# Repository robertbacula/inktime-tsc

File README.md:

# InkTime v6 - Smartwatch Open Hardware cu E-Paper

InkTime v6 este un proiect hardware open-source de smartwatch bazat pe nRF52840, optimizat pentru consum redus, autonomie mare si integrare mecanica compacta. Documentatia de mai jos este structurata pentru review tehnic si include arhitectura sistemului, BOM, maparea pinilor, analiza de consum si observatii de design.

## Cuprins

- [Diagrama bloc](#diagrama-bloc)
- [Bill of Materials (BOM)](#bill-of-materials-bom)
- [Functionalitate hardware detaliata](#functionalitate-hardware-detaliata)
- [Maparea pinilor nRF52840](#maparea-pinilor-nrf52840)
- [Analiza consumului de energie](#analiza-consumului-de-energie)
- [Design PCB si integrare mecanica](#design-pcb-si-integrare-mecanica)
- [Design log si observatii pentru review](#design-log-si-observatii-pentru-review)
- [Structura repository-ului](#structura-repository-ului)
- [Licenta](#licenta)

## Diagrama bloc

Diagrama bloc este prezentata ca imagine:

Flux de functionare:

1. USB-C alimenteaza incarcatorul BQ25180 si bateria LiPo.
2. Din baterie se genereaza rail-ul de 3.3V (RT6160A), comutat catre sarcina prin PMOS.
3. nRF52840 colecteaza date de la IMU/fuel gauge si controleaza display-ul prin SPI.
4. Pentru notificari locale, nRF52840 activeaza DRV2605 care comanda motorul haptic.
5. BLE asigura schimb de date si configurare cu telefonul.

## Bill of Materials (BOM)

Tabelul de mai jos acopera componentele principale. Pentru pasivele individuale, consultati schema si listele de asamblare exportate din CAD.

| #   | Ref  | Componenta              | Cod / Valoare     | JLC Parts                                                                                                 | Datasheet                                                                                                        |
| --- | ---- | ----------------------- | ----------------- | --------------------------------------------------------------------------------------------------------- | ---------------------------------------------------------------------------------------------------------------- |
| 1   | U1   | MCU BLE                 | nRF52840-QIAA     | [C190794](https://jlcpcb.com/parts/componentSearch?isSearch=true&searchTxt=nRF52840)                      | [nRF52840 PS](https://infocenter.nordicsemi.com/pdf/nRF52840_PS_v1.8.pdf)                                        |
| 2   | IC2  | Li-Ion Charger          | BQ25180YBGR       | [C2682092](https://jlcpcb.com/parts/componentSearch?isSearch=true&searchTxt=BQ25180)                      | [TI BQ25180](https://www.ti.com/lit/ds/symlink/bq25180.pdf)                                                      |
| 3   | IC9  | Buck DC/DC              | RT6160AWSC        | [C2828036](https://jlcpcb.com/parts/componentSearch?isSearch=true&searchTxt=RT6160A)                      | [Richtek RT6160A](https://www.richtek.com/assets/product_file/RT6160A/DS6160A-05.pdf)                            |
| 4   | U3   | Fuel Gauge              | MAX17048G+T10     | [C2682766](https://jlcpcb.com/parts/componentSearch?isSearch=true&searchTxt=MAX17048)                     | [MAX17048/49](https://datasheets.maximintegrated.com/en/ds/MAX17048-MAX17049.pdf)                                |
| 5   | IC3  | IMU                     | BMA423            | [C2831316](https://jlcpcb.com/parts/componentSearch?isSearch=true&searchTxt=BMA423)                       | [Bosch BMA423](https://www.bosch-sensortec.com/products/motion-sensors/accelerometers/bma423/)                   |
| 6   | IC1  | Driver haptic           | DRV2605YZFR       | [C527680](https://jlcpcb.com/parts/componentSearch?isSearch=true&searchTxt=DRV2605)                       | [TI DRV2605](https://www.ti.com/lit/ds/symlink/drv2605.pdf)                                                      |
| 7   | D1   | Protectie ESD USB       | USBLC6-2SC6Y      | [C7519](https://jlcpcb.com/parts/componentSearch?isSearch=true&searchTxt=USBLC6-2SC6Y)                    | [ST USBLC6-2](https://www.st.com/resource/en/datasheet/usblc6-2.pdf)                                             |
| 8   | Q1   | PMOS load switch        | DMG2305UX-7       | [C150812](https://jlcpcb.com/parts/componentSearch?isSearch=true&searchTxt=DMG2305UX)                     | [DMG2305UX](https://www.diodes.com/assets/Datasheets/DMG2305UX.pdf)                                              |
| 9   | Q3   | N-MOS (motor/periferic) | SI1308EDL-T1-GE3  | [C515086](https://jlcpcb.com/parts/componentSearch?isSearch=true&searchTxt=SI1308EDL)                     | [SI1308EDL](https://www.vishay.com/docs/68743/si1308edl.pdf)                                                     |
| 10  | J1   | FPC conector EPD        | 503480-2400 (24p) | [C585393](https://jlcpcb.com/parts/componentSearch?isSearch=true&searchTxt=503480-2400)                   | [Molex 503480](https://www.molex.com/pdm_docs/sd/5034802400_sd.pdf)                                              |
| 11  | J4   | USB-C conector          | KH-TYPE-C-16P     | [C2765186](https://jlcpcb.com/parts/componentSearch?isSearch=true&searchTxt=KH-TYPE-C-16P)                | [USB Type-C Spec](https://www.usb.org/document-library/usb-type-cr-cable-and-connector-specification-release-22) |
| 12  | ANT1 | Antena chip 2.4GHz      | 2450AT18B100E     | [Search JLC](https://jlcpcb.com/parts/componentSearch?isSearch=true&searchTxt=2450AT18B100E)              | [Johanson 2450AT18B100E](https://www.johansontechnology.com/datasheets/2450AT18B100E.pdf)                        |
| 13  | J2   | Header debug            | TC2030-IDC        | [Search JLC](https://jlcpcb.com/parts/componentSearch?isSearch=true&searchTxt=TC2030)                     | [Tag-Connect TC2030](https://www.tag-connect.com/wp-content/uploads/bsk-pdf-manager/TC2030-IDC-NL-10_NL_1.pdf)   |
| 14  | X1   | Cristal HF              | 32MHz             | [Search JLC](https://jlcpcb.com/parts/componentSearch?isSearch=true&searchTxt=32MHz%20crystal%202016)     | [Exemplu 32MHz](https://www.ecsxtal.com/store/pdf/ECS-160-12-33Q.pdf)                                            |
| 15  | X2   | Cristal LF              | 32.768kHz         | [Search JLC](https://jlcpcb.com/parts/componentSearch?isSearch=true&searchTxt=32.768kHz%20crystal%203215) | [Exemplu 32.768kHz](https://www.abracon.com/Resonators/ABS07.pdf)                                                |

## Functionalitate hardware detaliata

### 1) Procesare si conectivitate - nRF52840

- CPU: ARM Cortex-M4F @ 64MHz
- Memorie: 1MB Flash, 256KB RAM
- Radio: BLE 5.x la 2.4GHz
- Interfete folosite in proiect: SPI, I2C, GPIO, USB FS, SWD

Rol functional:

- ruleaza logica aplicatiei si machine-state-ul ceasului
- centralizeaza datele de la senzori
- controleaza secventa de refresh pentru e-paper
- gestioneaza notificari BLE si feedback haptic

### 2) Display e-paper (1.54") + etaj driver

Display-ul e-paper este comandat pe SPI, cu semnale separate de control (`DC`, `RST`, `BUSY`, `CS`). Avantajul major este consumul aproape zero in stare statica; energia se consuma aproape exclusiv la refresh.

Interfata:

- SPI pentru payload grafic
- GPIO pentru sincronizare/stare (`BUSY`) si comenzi

### 3) IMU BMA423

IMU-ul este conectat pe I2C si utilizat pentru:

- step counting
- wake-on-motion / wrist raise
- detectie evenimente contextuale

Poate genera intreruperi catre MCU pentru reducerea polling-ului si optimizare de consum.

### 4) Management baterie - BQ25180 + MAX17048 + RT6160A

- BQ25180: incarcare LiPo din VBUS (USB-C)
- MAX17048: monitorizare starea bateriei (SOC, tensiune)
- RT6160A: conversie stabila catre 3.3V pentru sistem

Acest lant permite operare corecta atat pe USB, cat si pe baterie, cu telemetrie energetica pentru estimarea autonomiei.

### 5) Haptic - DRV2605 + motor

DRV2605 genereaza profile haptice controlate de MCU (I2C + trigger), iar etajul de putere comuta motorul pentru feedback la notificari, alarme si interactiuni UI.

### 6) USB-C, protectie ESD si debug

- USB-C ofera VBUS pentru incarcare si (optional) date USB FS.
- USBLC6-2 reduce riscul de defect la descarcari electrostatice pe D+/D-.
- Header-ul TC2030 expune SWD pentru flash/debug si test de productie.

## Maparea pinilor nRF52840

Maparea de mai jos este cea utilizata in schema proiectului pentru functiile principale.

| Pin nRF52840  | Semnal / Componenta | Interfata | Directie | Motiv alegere                          |
| ------------- | ------------------- | --------- | -------- | -------------------------------------- |
| P0.02         | EPD_SCK             | SPI       | Out      | Clock stabil pentru transfer display   |
| P0.03         | EPD_MOSI            | SPI       | Out      | Date catre e-paper                     |
| P0.28         | EPD_MISO            | SPI       | In       | Citire status/date display             |
| P0.29         | EPD_CS              | GPIO/SPI  | Out      | Selectie dispozitiv e-paper            |
| P0.04         | EPD_DC              | GPIO      | Out      | Selectie data/comanda                  |
| P0.05         | EPD_RST             | GPIO      | Out      | Reset hardware display                 |
| P0.06         | EPD_BUSY            | GPIO      | In       | Sincronizare pe stare busy             |
| P0.26         | I2C_SDA             | I2C       | I/O      | Magistrala comuna senzori/power        |
| P0.27         | I2C_SCL             | I2C       | Out      | Clock I2C comun                        |
| P0.13         | SW_UP               | GPIO IRQ  | In       | Buton up, interrupt la apasare         |
| P0.14         | SW_ENT              | GPIO IRQ  | In       | Buton enter, UI action                 |
| P0.15         | SW_DN               | GPIO IRQ  | In       | Buton down, navigare                   |
| P0.18         | USB_D-              | USB FS    | I/O      | Linie USB dedicata (minus)             |
| P0.20         | USB_D+              | USB FS    | I/O      | Linie USB dedicata (plus)              |
| P0.00 / P0.01 | XL1 / XL2           | LFCLK     | I/O      | Cristal 32.768kHz pentru RTC low-power |
| XC1 / XC2     | X1 32MHz            | HFCLK     | I/O      | Ceas principal CPU/RF                  |
| SWDIO         | SWD_DATA            | SWD       | I/O      | Programare si debugging                |
| SWDCLK        | SWD_CLK             | SWD       | In       | Ceas SWD                               |
| SWO           | SWO_TRACE           | SWD       | Out      | Trace/telemetrie debug                 |
| ANT           | Antena BLE          | RF        | Out      | Iesire RF catre retea de matching      |

Rationale general pentru mapare:

1. SPI-ul display-ului este grupat compact pentru rutare scurta si integritate buna a semnalelor.
2. Toate perifericele lente (IMU, fuel gauge, haptic) sunt pe I2C comun pentru economie de pini.
3. Butoanele sunt pe GPIO-uri configurabile cu intreruperi, pentru wake-up din low power.
4. USB foloseste pinii dedicati ai MCU pentru compatibilitate fizica si software.

## Analiza consumului de energie

Estimare orientativa pe scenariu "smartwatch normal" (ecran actualizat periodic, BLE advertising, wake pe evenimente):

| Bloc                 | Curent activ | Curent sleep/idle | Duty cycle estimat | Curent mediu |
| -------------------- | -----------: | ----------------: | -----------------: | -----------: |
| nRF52840 (CPU + BLE) |  3.2mA-4.8mA |             1.5uA |               5-6% |       ~210uA |
| E-Paper (refresh)    |        ~15mA |       ~0uA static |               0.5% |        ~75uA |
| BMA423               |       ~150uA |             ~14uA |          10% activ |        ~28uA |
| MAX17048             |         23uA |              23uA |               100% |         23uA |
| DRV2605 + motor      |   ~50mA varf |           ~0.25uA |               0.1% |        ~50uA |
| RT6160A quiescent    |            - |             ~25uA |               100% |         25uA |
| **Total estimat**    |            - |                 - |                  - |   **~410uA** |

Pentru baterie de 250mAh:

- autonomie teoretica: `250mAh / 0.41mA = ~609h` (~25 zile)
- cu profil agresiv de sleep si refresh rar: 30-40+ zile (in functie de firmware si trafic BLE)

## Design PCB si integrare mecanica

### PCB

- layout realizat in fisierele `Hardware/project-tsc.sch` si `Hardware/project-tsc-2d-pcb.brd`
- topologia include zona RF dedicata, sectiune alimentare separata si trasee de semnal scurte catre conectorul EPD
- protectie ESD pe USB si puncte de test pentru bring-up

### Integrare mecanica

- modele 3D disponibile in `Mechanical/InkTime3D.f3z` si `Mechanical/InkTime3D.step`
- verificari importante: inaltime baterie, spatiu FPC display, pozitie butoane laterale, clearance pentru motorul haptic

## Design log si observatii pentru review

Design log (sintetic):

1. Definire arhitectura (MCU, putere, senzori, afisaj)
2. Captura schema si validare ERC
3. Placement cu prioritizare RF/power/display
4. Routing + optimizari DRC/ground return
5. Export productie si validare mecanica 3D

Observatii utile pentru review:

- verificati zona antenei: keepout de cupru sub antenna + matching network conform recomandari vendor
- confirmati polaritatea pentru bateria LiPo si sensul diodei Schottky
- verificati secventa de power-up EPD in firmware, pentru a evita refresh instabil
- recomandat test incremental: power rail -> SWD -> I2C -> EPD -> BLE

## Structura repository-ului

```text
inktime-tsc/
|- Hardware/
|  |- project-tsc.sch
|  |- project-tsc-2d-pcb.brd
|- Images/
|  |- 3dpcb.jpg
|  |- inktime-full-watch.jpg
|  |- inktime-3d-expanded-view.jpg
|  |- inktime-watch-no-screen.jpg
|- Manufacturing/
|  |- inktime_gerber.zip
|- Mechanical/
|  |- InkTime3D.f3z
|  |- InkTime3D.step
|- LICENSE
|- README.md
```

## Licenta

Proiectul este distribuit conform fisierului `LICENSE` din acest repository.

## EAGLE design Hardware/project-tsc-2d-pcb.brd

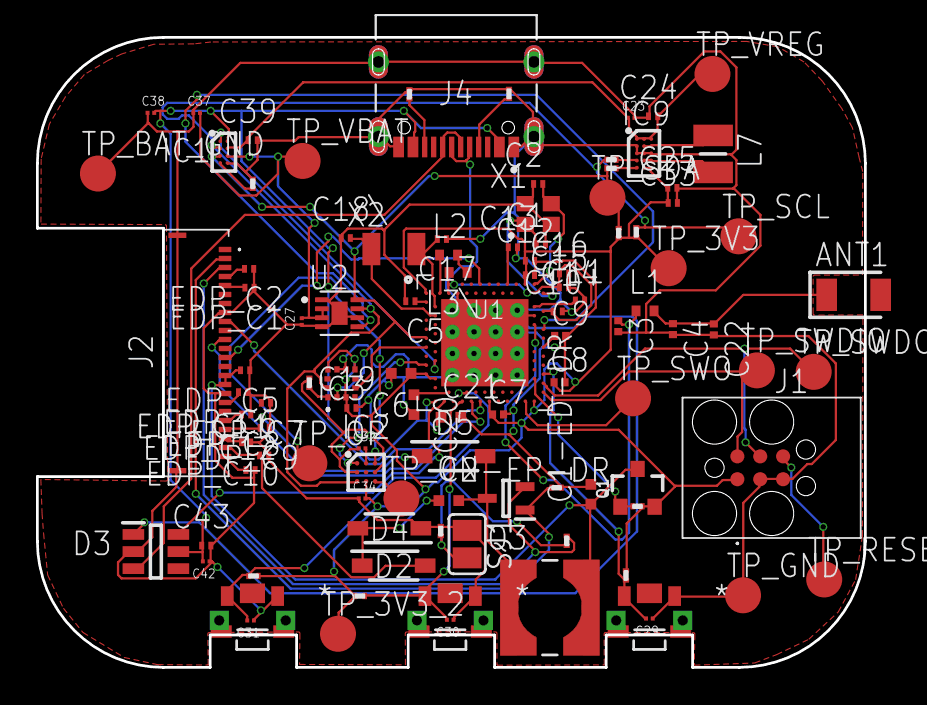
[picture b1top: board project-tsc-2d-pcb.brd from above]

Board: 2 copper layers, 46.0 x 35.0 mm, 105 parts (0 on the bottom side), 70 nets.

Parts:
ANT1: 2450AT18B100E; 2450AT18B100E_ANTC3216X140N
C1, C2, C17, C18\: 12pF; NORDIC_NRF_3_RESC0201_L
C1-ED-DR: 10uF; NORDIC_NRF_3_RESC0402_N
C2-EP-DR, C6, C20, C21: 4.7uF; NORDIC_NRF_3_RESC0402_N
C3, C4: 1pF; NORDIC_NRF_3_RESC0201_N
C5, C12, C19: 100nF; NORDIC_NRF_3_RESC0201_L
C7, C8: 100nF; NORDIC_NRF_3_RESC0201_N
C9: 820pF; NORDIC_NRF_3_RESC0201_N
C10, C13: N.C.; NORDIC_NRF_3_RESC0201_L
C11: 100pF; NORDIC_NRF_3_RESC0201_L
C14, C43: 4.7uF; NORDIC_NRF_3_RESC0201_L
C15: 1.0uF; NORDIC_NRF_3_RESC0201_L
C16: 47nF; NORDIC_NRF_3_RESC0201_L
C22: N.C.; NORDIC_NRF_3_RESC0201_N
C23, C27, C34, C42: 0.1uF; GRM011R60J152KE01L_2_CAPC0201X13N
C24, C39: 10uF; NORDIC_NRF_3_RESC0201_L
C25, C33: 22uF; NORDIC_NRF_3_RESC0201_L
C29, C30, C31, C32, C37, C38: 1uF; GRM011R60J152KE01L_2_CAPC0201X13N
D2, D4, D5: MBR0530; ESP32_C6_LIBRARY_5_SOD3716X135N
D3: USBLC6-2SC6Y; ESP32_C6_LIBRARY_3_SOT95P280X145-6N
EDP_C1, EDP_C2: 10uF; NORDIC_NRF_3_RESC0201_L
EDP_C5: 0.1uF/50V; NORDIC_NRF_3_RESC0201_L
EDP_C6, EDP_C7, EDP_C8, EDP_C9, EDP_C10, EDP_C11, EDP_C12: 1uF/50V; NORDIC_NRF_3_RESC0201_L
IC1: BQ25180YBGR; BQ25180YBGR_BGA8C40P2X4_100X155X50
IC2: DRV2605YZFR; DRV2605YZFR_BGA9C50P3X3_144X144X62
IC3: BMA421; BMA423_BMA423
IC9: RT6160AWSC; RT6160AWSC_BGA15C40P3X5_140X230X60
J1: TC2030-IDC_TC2030-IDC; TC2030-IDC_TC2030IDC
J2: 503480-2400_503480-2400; 503480-2400_5034802400
J4: KH-TYPE-C-16P; KH-TYPE-C-16P_KINGHELM_KH-TYPE-C-16P
L1: 3.9nH; NORDIC_NRF_2_RESC0402_L
L2: 10uH; NORDIC_NRF_2_RESC0402_L
L3\: 15nH; NORDIC_NRF_2_RESC0402_L
L5: 68uH; ESP32_C6_LIBRARY_2_IND_4828-WE-TPC_WRE
L7: FTC252012SR47MBCA; MLP2016SR47MT0S1_INDC2016X100N
Q1: 20V/4.2A/52mΩ/1.4W; ESP32_C6_LIBRARY_4_ESP32_C6_LIBRARY_4_ESP32_C6_LIBRARY_4_ES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
Q3: SI1308EDL-T1-GE3; ESP32_C6_LIBRARY_6_SOT65P210X110-3N
R1, R2, R2_EP_DR, R5, R7, R8, R9: 10K; CPF0201D7K68C1_0201
R1_EP_DR1: 0.47; CPF0201D7K68C1_0201
R1_USB, R2_USB: 5K1; CPF0201D7K68C1_0201
R3: 0; CPF0201D7K68C1_0201
R17, R18: 3K3; CPF0201D7K68C1_0201
R_PWR_EPD: 10K; CPF0201D7K68C1_0201
R_TYPE_SEL: 2.2; CPF0201D7K68C1_0201
SJ1: ESP32_C6_LIBRARY_7_JUMPER_SJ
SW_DN: 2025-10-22_07-23-44_LIBRARY_EVP-AKE31ASW_EVP-AKE3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; 2025-10-22_07-23-44_LIBRARY_SW_EVP-AKE31A_PAN
SW_ENT: 2025-10-22_07-23-44_LIBRARY_EVP-AKE31ASW_EVP-AKE3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; 2025-10-22_07-23-44_LIBRARY_SW_EVP-AKE31A_PAN
SW_UP: 2025-10-22_07-23-44_LIBRARY_EVP-AKE31ASW_EVP-AKE3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; 2025-10-22_07-23-44_LIBRARY_SW_EVP-AKE31A_PAN
TP_3V3, TP_3V3_2: HECTOR_WATCH_1_TPTP20R; HECTOR_WATCH_1_TP20R
TP_BAT_GND: HECTOR_WATCH_1_TPTP20R; HECTOR_WATCH_1_TP20R
TP_GND: HECTOR_WATCH_1_TPTP20R; HECTOR_WATCH_1_TP20R
TP_ON: HECTOR_WATCH_1_TPTP20R; HECTOR_WATCH_1_TP20R
TP_OP: HECTOR_WATCH_1_TPTP20R; HECTOR_WATCH_1_TP20R
TP_RESET: HECTOR_WATCH_1_TPTP20R; HECTOR_WATCH_1_TP20R
TP_SCL: HECTOR_WATCH_1_TPTP20R; HECTOR_WATCH_1_TP20R
TP_SDA: HECTOR_WATCH_1_TPTP20R; HECTOR_WATCH_1_TP20R
TP_SWDCLK: HECTOR_WATCH_1_TPTP20R; HECTOR_WATCH_1_TP20R
TP_SWDIO: HECTOR_WATCH_1_TPTP20R; HECTOR_WATCH_1_TP20R
TP_SWO: HECTOR_WATCH_1_TPTP20R; HECTOR_WATCH_1_TP20R
TP_VBAT: HECTOR_WATCH_1_TPTP20R; HECTOR_WATCH_1_TP20R
TP_VREG: HECTOR_WATCH_1_TPTP20R; HECTOR_WATCH_1_TP20R
U1: NRF52840_QF; NORDIC_NRF_4_AQFN50P700X700X85_HS-74N
U2: ESP32_C6_LIBRARY_MAX17048G+T10; ESP32_C6_LIBRARY_SON50P200X200X80-9N
X1: 32MHz; NORDIC_NRF_BT-XTAL_2016_N
X2: 32.726kHz; NORDIC_NRF_1_XTAL_3215_N

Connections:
3V1: C5.1, U1.P$C1
3V3: C6.1, C7.1, C8.1, C12.1, C14.1, C19.1, C25.1, C33.1, C34.2, IC2.C2, IC3.3, IC3.7, IC3.10, IC9.E2, IC9.E3, J1.1, Q1.2, R5.1, R7.1, R8.1, R17.2, R18.2, R_PWR_EPD.1, TP_3V3.TP, TP_3V3_2.TP, U1.P$A22, U1.P$AD14, U1.P$AD23, U1.P$B1, U1.P$W1, U1.P$Y2
ALERT: U1.P$J24, U2.5
D+: D3.4, U1.P$AD6
D-: D3.6, U1.P$AD4
DN: D3.1, J4.A7, J4.B7
DP: D3.3, J4.A6, J4.B6
EPD_3V3: C1-ED-DR.1, EDP_C5.2, J2.15, J2.16, L5.2, Q1.3
EPD_BUSY: J2.9, U1.P$AD12
EPD_CS: J2.12, U1.P$K2
EPD_DC: J2.11, U1.P$AD10
EPD_RST: J2.10, U1.P$AC11
ESP_3V1: EDP_C6.2, J2.18
ESP_3V2: EDP_C7.2, J2.19
ESP_3V4: EDP_C8.2, J2.20
ESP_3V6: EDP_C10.2, J2.22
GDR: J2.2, Q3.1, R2_EP_DR.1
GND: C1.2, C1-ED-DR.2, C2.1, C3.2, C4.2, C5.2, C6.2, C7.2, C8.2, C9.2, C10.2, C11.2, C12.2, C13.2, C14.2, C15.2, C16.2, C17.1, C18\.1, C19.2, C20.2, C21.2, C22.2, C23.2, C24.1, C25.2, C27.1, C29.1, C30.1, C31.1, C32.1, C33.2, C34.1, C37.1, C38.1, C39.2, C42.1, C43.2, D3.2, D4.1, EDP_C1.1, EDP_C2.1, EDP_C5.1, EDP_C6.1, EDP_C7.1, EDP_C8.1, EDP_C9.1, EDP_C10.1, EDP_C11.2, EDP_C12.2, IC1.D2, IC2.B1, IC2.B3, IC3.8, IC3.9, IC9.B1, IC9.C1, IC9.C2, IC9.C3, J1.3, J1.5, J2.8, J2.17, J2.MP1, J2.MP2, J4.A1_B12, J4.A12_B1, J4.SH1, J4.SH2, J4.SH3, J4.SH4, R1_USB.1, R2_EP_DR.2, R2_USB.2, R3.1, R9.1, R_TYPE_SEL.2, SJ1.1, SW_DN.1, SW_ENT.1, SW_UP.1, TP_BAT_GND.TP, TP_GND.TP, U1.P$74, U1.P$75, U1.P$76, U1.P$77, U1.P$78, U1.P$79, U1.P$80, U1.P$81, U1.P$82, U1.P$83, U1.P$84, U1.P$85, U1.P$86, U1.P$87, U1.P$88, U1.P$89, U1.P$90, U1.P$B7, U1.P$F23, U2.1, U2.4, U2.6, U2.9, X1.2, X1.4
GND1: C17.2, U1.P$D2, X2.2
GND2: C18\.2, U1.P$F2, X2.1
GND3: C2.2, U1.P$A23, X1.3
HAPTIC_EN: IC2.A1, U1.P$U1
IMU_INT1: IC3.5, U1.P$N1
IMU_INT2: IC3.6, U1.P$P2
LX1: IC9.B2, IC9.B3, L7.1
LX2: IC9.D2, IC9.D3, L7.2
MOSI: J2.14, U1.P$B13
unnamed: L2.1, U1.P$B3
unnamed: L2.2, L3\.1
unnamed: C10.1, C15.1, C16.1, L3\.2, U1.P$B5, U1.P$E24
unnamed: R1_EP_DR1.2, R_TYPE_SEL.1, SJ1.2
unnamed: IC1.D1, R9.2
unnamed: C2-EP-DR.2, D5.2, L5.1, Q3.3
unnamed: C2-EP-DR.1, D2.1, D4.2
unnamed: J4.A5, R1_USB.2
unnamed: J4.B5, R2_USB.1
unnamed: EDP_C2.2, J2.4
unnamed: EDP_C1.2, J2.5
unnamed: C32.2, IC2.A2
unnamed: C13.1, U1.P$A18
unnamed: C11.1, U1.P$D23
unnamed: C1.1, U1.P$B24, X1.1
unnamed: IC9.D1, R1.2
unnamed: IC9.E1, R2.2
unnamed: EDP_C12.1, J2.24
unnamed: IC3.1, R3.2
unnamed: C20.1, U1.P$AC5
unnamed: C9.1, U1.P$N24
unnamed: ANT1.1, C4.1, C22.1, L1.2
unnamed: C3.1, L1.1, U1.P$H23
OUT+: IC2.A3, TP_OP.TP
OUT-: IC2.C3, TP_ON.TP
P0.13: C30.2, R5.2, SW_UP.2, U1.P$AD8
P0.14: C31.2, R8.2, SW_ENT.2, U1.P$AC9
P1.01: Q1.1, R_PWR_EPD.2, U1.P$Y23
P1.02: C29.2, R7.2, SW_DN.2, U1.P$W24
PMIC_INT: IC1.A1, U1.P$T2
PREVGH: D5.1, EDP_C9.2, J2.21
PREVGL: D2.2, EDP_C11.1, J2.23
RESE: J2.3, Q3.2, R1_EP_DR1.1
RESET: J1.6, TP_RESET.TP, U1.P$AC13
SCK: J2.13, U1.P$A12
SCL: IC1.B1, IC2.C1, IC3.12, R1.1, R17.1, TP_SCL.TP, U1.P$M2, U2.7
SDA: IC1.C1, IC2.B2, IC3.2, R2.1, R18.1, TP_SDA.TP, U1.P$L1, U2.8
SWDCLK: J1.4, TP_SWDCLK.TP, U1.P$AA24
SWDIO: J1.2, TP_SWDIO.TP, U1.P$AC24
SWO: TP_SWO.TP, U1.P$AD22
VBAT: C27.2, C37.2, IC1.C2, TP_VBAT.TP, U2.2, U2.3
VBUS: C21.1, C38.2, C42.2, C43.1, D3.5, IC1.A2, J4.A4_B9, J4.A9_B4, U1.P$AD2
VREG: C23.1, C24.2, C39.1, IC1.B2, IC9.A1, IC9.A2, IC9.A3, TP_VREG.TP

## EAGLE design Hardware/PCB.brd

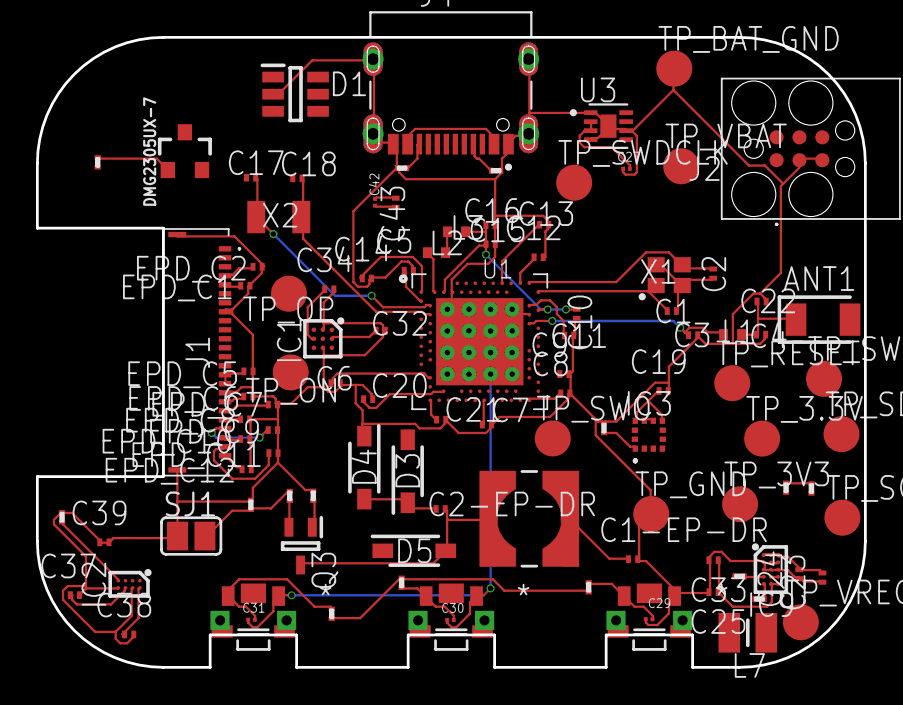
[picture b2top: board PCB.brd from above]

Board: 2 copper layers, 46.0 x 35.0 mm, 105 parts (0 on the bottom side), 63 nets.

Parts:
ANT1: 2450AT18B100E_2450AT18B100E; 2450AT18B100E_ANTC3216X140N
C1, C2, C17, C18: 12pF; NORDIC_NRF_3_RESC0201_L
C1-EP-DR: 10µF; NORDIC_NRF_3_RESC0201_L
C2-EP-DR: 4.7µF/25V; NORDIC_NRF_3_RESC0201_L
C3, C4: 1pF; NORDIC_NRF_3_RESC0201_L
C5, C7, C8, C12, C19: 100nF; NORDIC_NRF_3_RESC0201_L
C6, C14, C20, C21: 4.7µF; NORDIC_NRF_3_RESC0201_L
C9: 820pF; NORDIC_NRF_3_RESC0201_L
C10, C13, C15, C22: N.C.; NORDIC_NRF_3_RESC0201_L
C11: 100pF; NORDIC_NRF_3_RESC0201_L
C16: 27nF; NORDIC_NRF_3_RESC0201_L
C23: 0.1uF; NORDIC_NRF_3_RESC0201_L
C24: 10uF; NORDIC_NRF_3_RESC0201_L
C25, C33: 22uF; NORDIC_NRF_3_RESC0201_L
C27, C29, C30, C31, C42: GRM011R60J152KE01L_2_GRM011R60J152KE01L; GRM011R60J152KE01L_2_CAPC0201X13N
C32: 1µF; NORDIC_NRF_3_RESC0201_L
C34: 0.1µF; NORDIC_NRF_3_RESC0201_L
C37, C38, C39: NORDIC_NRF_3_RESC0201_L
C43: 4.7uF; NORDIC_NRF_3_RESC0201_L
D1: ESP32_C6_LIBRARY_3_USBLC6-2SC6Y; ESP32_C6_LIBRARY_3_SOT95P280X145-6N
D3, D4, D5: ESP32_C6_LIBRARY_5_MBR0530; ESP32_C6_LIBRARY_5_SOD3716X135N
DMG2305UX-7: 20V/4.2A/52mΩ/1.4W; ESP32_C6_LIBRARY_4_ESP32_C6_LIBRARY_4_ESP32_C6_LIBRARY_4_ES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
EPD_C1, EPD_C2: 1uF/50V; NORDIC_NRF_3_RESC0201_L
EPD_C5, EPD_C6, EPD_C7, EPD_C8, EPD_C9, EPD_C10, EPD_C11, EPD_C12: 0.1uF/50V; NORDIC_NRF_3_RESC0201_L
IC1: DRV2605YZFR_DRV2605YZFR; DRV2605YZFR_BGA9C50P3X3_144X144X62
IC2: BQ25180YBGR_BQ25180YBGR; BQ25180YBGR_BGA8C40P2X4_100X155X50
IC3: BMA423_BMA423
IC9: RT6160AWSC_RT6160AWSC; RT6160AWSC_BGA15C40P3X5_140X230X60
J1: 503480-2400_503480-2400; 503480-2400_5034802400
J2: TC2030-IDC_TC2030-IDC; TC2030-IDC_TC2030IDC
J4: KH-TYPE-C-16P_KH-TYPE-C-16P; KH-TYPE-C-16P_KINGHELM_KH-TYPE-C-16P
L1: 3.9nH; NORDIC_NRF_2_RESC0402_L
L2: 10µH; NORDIC_NRF_2_RESC0402_L
L3: 15nH; NORDIC_NRF_2_RESC0402_L
L5: 68uH; ESP32_C6_LIBRARY_2_IND_4828-WE-TPC_WRE
L7: MLP2016SR47MT0S1_FTC252012SR47MBCA; MLP2016SR47MT0S1_INDC2016X100N
Q3: ESP32_C6_LIBRARY_6_SI1308EDL-T1-GE3; ESP32_C6_LIBRARY_6_SOT65P210X110-3N
R1_EP_DR, R1_USB, R2, R2_EP_DR, R2_USB, R3, R4, R5, R7, R8, R9, R17, R18: ERA-1AEB3401C_CPF0201D7K68C1; ERA-1AEB3401C_0201
R_PWR_EPD: ERA-1AEB3401C_CPF0201D7K68C1; ERA-1AEB3401C_0201
R_TYPE_SEL: ERA-1AEB3401C_CPF0201D7K68C1; ERA-1AEB3401C_0201
SJ1: ESP32_C6_LIBRARY_7_JUMPER_SJ
SW_DN: 2025-10-22_07-23-44_LIBRARY_EVP-AKE31ASW_EVP-AKE3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; 2025-10-22_07-23-44_LIBRARY_SW_EVP-AKE31A_PAN
SW_ENT: 2025-10-22_07-23-44_LIBRARY_EVP-AKE31ASW_EVP-AKE3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; 2025-10-22_07-23-44_LIBRARY_SW_EVP-AKE31A_PAN
SW_UP: 2025-10-22_07-23-44_LIBRARY_EVP-AKE31ASW_EVP-AKE3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; 2025-10-22_07-23-44_LIBRARY_SW_EVP-AKE31A_PAN
TP_3.3V, TP_3V3: HECTOR_WATCH_1_TPTP20R; HECTOR_WATCH_1_TP20R
TP_BAT_GND: HECTOR_WATCH_1_TPTP20R; HECTOR_WATCH_1_TP20R
TP_GND: HECTOR_WATCH_1_TPTP20R; HECTOR_WATCH_1_TP20R
TP_ON: HECTOR_WATCH_1_TPTP20R; HECTOR_WATCH_1_TP20R
TP_OP: HECTOR_WATCH_1_TPTP20R; HECTOR_WATCH_1_TP20R
TP_RESET: HECTOR_WATCH_1_TPTP20R; HECTOR_WATCH_1_TP20R
TP_SCL: HECTOR_WATCH_1_TPTP20R; HECTOR_WATCH_1_TP20R
TP_SDA: HECTOR_WATCH_1_TPTP20R; HECTOR_WATCH_1_TP20R
TP_SWDCLK: HECTOR_WATCH_1_TPTP20R; HECTOR_WATCH_1_TP20R
TP_SWDIO: HECTOR_WATCH_1_TPTP20R; HECTOR_WATCH_1_TP20R
TP_SWO: HECTOR_WATCH_1_TPTP20R; HECTOR_WATCH_1_TP20R
TP_VBAT: HECTOR_WATCH_1_TPTP20R; HECTOR_WATCH_1_TP20R
TP_VREG: HECTOR_WATCH_1_TPTP20R; HECTOR_WATCH_1_TP20R
U1: NORDIC_NRF_4_NRF52840_QF; NORDIC_NRF_4_AQFN50P700X700X85_HS-74N
U3: ESP32_C6_LIBRARY_MAX17048G+T10; ESP32_C6_LIBRARY_SON50P200X200X80-9N
X1: NORDIC_NRF_BT-XTAL_2016_N
X2: 32.768kHz; NORDIC_NRF_1_XTAL_3215_N

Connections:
GND: C1-EP-DR.2, C3.2, C4.2, C5.2, C6.2, C7.2, C8.2, C9.2, C10.2, C11.2, C12.2, C13.2, C14.2, C15.2, C16.2, C19.2, C20.2, C21.2, C22.2, C23.1, C24.1, C25.2, C27.1, C29.1, C30.1, C31.1, C32.2, C33.2, C34.2, C37.2, C38.2, C39.1, C39.2, D1.2, D4.1, EPD_C1.1, EPD_C2.1, EPD_C5.1, EPD_C6.1, EPD_C7.1, EPD_C8.1, EPD_C9.1, EPD_C10.1, EPD_C11.1, EPD_C12.1, IC1.B1, IC1.B3, IC2.B2, IC2.D2, IC9.B1, IC9.C1, IC9.C2, IC9.C3, J1.8, J1.17, J1.MP1, J1.MP2, J2.3, J2.5, J4.A1_B12, J4.A12_B1, J4.SH1, J4.SH2, J4.SH3, J4.SH4, R1_USB.2, R2_EP_DR.1, R2_USB.2, R3.1, R9.1, R_TYPE_SEL.1, SJ1.1, SW_DN.1, SW_ENT.1, SW_UP.1, TP_BAT_GND.TP, TP_GND.TP, U1.P$74, U1.P$75, U1.P$76, U1.P$77, U1.P$78, U1.P$79, U1.P$80, U1.P$81, U1.P$82, U1.P$83, U1.P$84, U1.P$85, U1.P$86, U1.P$87, U1.P$88, U1.P$89, U1.P$90, U1.P$B7, U1.P$F23, U3.1, U3.4, U3.6, U3.9
GND1: R1_EP_DR.1, R_TYPE_SEL.2, SJ1.2
GND2: C29.2, R7.1, SW_DN.2
GND3: C31.2, R8.1, SW_ENT.2
GND4: C30.2, R5.1, SW_UP.2
unnamed: IC2.D1, R9.2
unnamed: C38.1, IC2.A2
unnamed: C37.1, IC2.C2
unnamed: C23.2, C24.2, IC9.A1, IC9.A2, IC9.A3
unnamed: IC9.B2, IC9.B3
unnamed: IC9.D1, R4.2
unnamed: R17.1, R18.1
unnamed: IC9.D2, IC9.D3
unnamed: C25.1, C33.1, IC9.E2, IC9.E3
unnamed: IC9.E1, R2.2
unnamed: C19.1, IC3.7, IC3.10
unnamed: IC3.8, IC3.9
unnamed: IC3.1, R3.2
unnamed: C7.1, U1.P$AD14
unnamed: C21.1, U1.P$AD2
unnamed: C8.1, U1.P$AD23
unnamed: C3.1, L1.1, U1.P$H23
unnamed: ANT1.1, C4.1, C22.1, L1.2
unnamed: C10.1, C15.1, C16.1, L3.2, U1.P$B5, U1.P$E24
unnamed: C11.1, U1.P$D23
unnamed: C1.1, U1.P$B24, X1.1
unnamed: C2.1, U1.P$A23, X1.3
unnamed: C1.2, C2.2, X1.2, X1.4
unnamed: C12.1, U1.P$A22
unnamed: C13.1, U1.P$A18
unnamed: L2.2, L3.1
unnamed: L2.1, U1.P$B3
unnamed: C20.1, U1.P$AC5
unnamed: C6.1, U1.P$W1, U1.P$Y2
unnamed: C14.1, U1.P$B1
unnamed: C5.1, U1.P$C1
unnamed: C17.2, U1.P$D2, X2.1
unnamed: C18.2, U1.P$F2, X2.2
unnamed: C1-EP-DR.1, L5.2
unnamed: C2-EP-DR.2, D5.2, L5.1, Q3.3
unnamed: C2-EP-DR.1, D3.1, D4.2
unnamed: Q3.1, R2_EP_DR.2
unnamed: Q3.2, R1_EP_DR.2
unnamed: DMG2305UX-7.1, R_PWR_EPD.1
unnamed: C32.1, IC1.A2
unnamed: C34.1, IC1.C2
unnamed: R5.2, R7.2, R8.2
unnamed: C27.2, U3.2, U3.3
unnamed: EPD_C12.2, J1.24
unnamed: EPD_C2.2, J1.4
unnamed: EPD_C1.2, J1.5
unnamed: EPD_C5.2, J1.15, J1.16
unnamed: EPD_C11.2, J1.23
unnamed: EPD_C10.2, J1.22
unnamed: EPD_C9.2, J1.21
unnamed: EPD_C8.2, J1.20
unnamed: EPD_C7.2, J1.19
unnamed: EPD_C6.2, J1.18
unnamed: J4.A4_B9, J4.A9_B4
unnamed: J4.B5, R2_USB.1
unnamed: J4.A5, R1_USB.1
unnamed: C42.2, C43.1
unnamed: C42.1, C43.2

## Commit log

2026-04-10 added image to readme
2026-04-10 update mechanical and manufacturing
2026-04-19 review changes
2026-04-19 block diagram added
2026-04-19 added .cpl and .bom files

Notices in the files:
parts and their libraries:
COPYRIGHT: Copyright (C) 2024 Ultra Librarian. All rights reserved.
COPYRIGHT: Copyright (C) 2025 Ultra Librarian. All rights reserved.
